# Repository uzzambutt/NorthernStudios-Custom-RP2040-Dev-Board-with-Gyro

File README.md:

# NorthernStudios-Custom-RP2040-Dev-Board-with-Gyro

***Schematic***

## Images:
**Rendered Board**:

**Raw Routing**:

## Features
1: This dev board has a LED for power indicator.
2: This board has a 6-Axis Gyro + Accelerometer integrated in it. you can read the schematic to check it out.

## Caution:
> I have not routed the GPIO 0,1 and ADC 1 and 2 because of spacing problems. there was not enough space to route them because the accelerometer had covered most of that space. 

---
> Made By uzzam for NorthernStudios.
> Funded By HackClub.
> 04/12/2025
> uzzambutt1@outlook.com

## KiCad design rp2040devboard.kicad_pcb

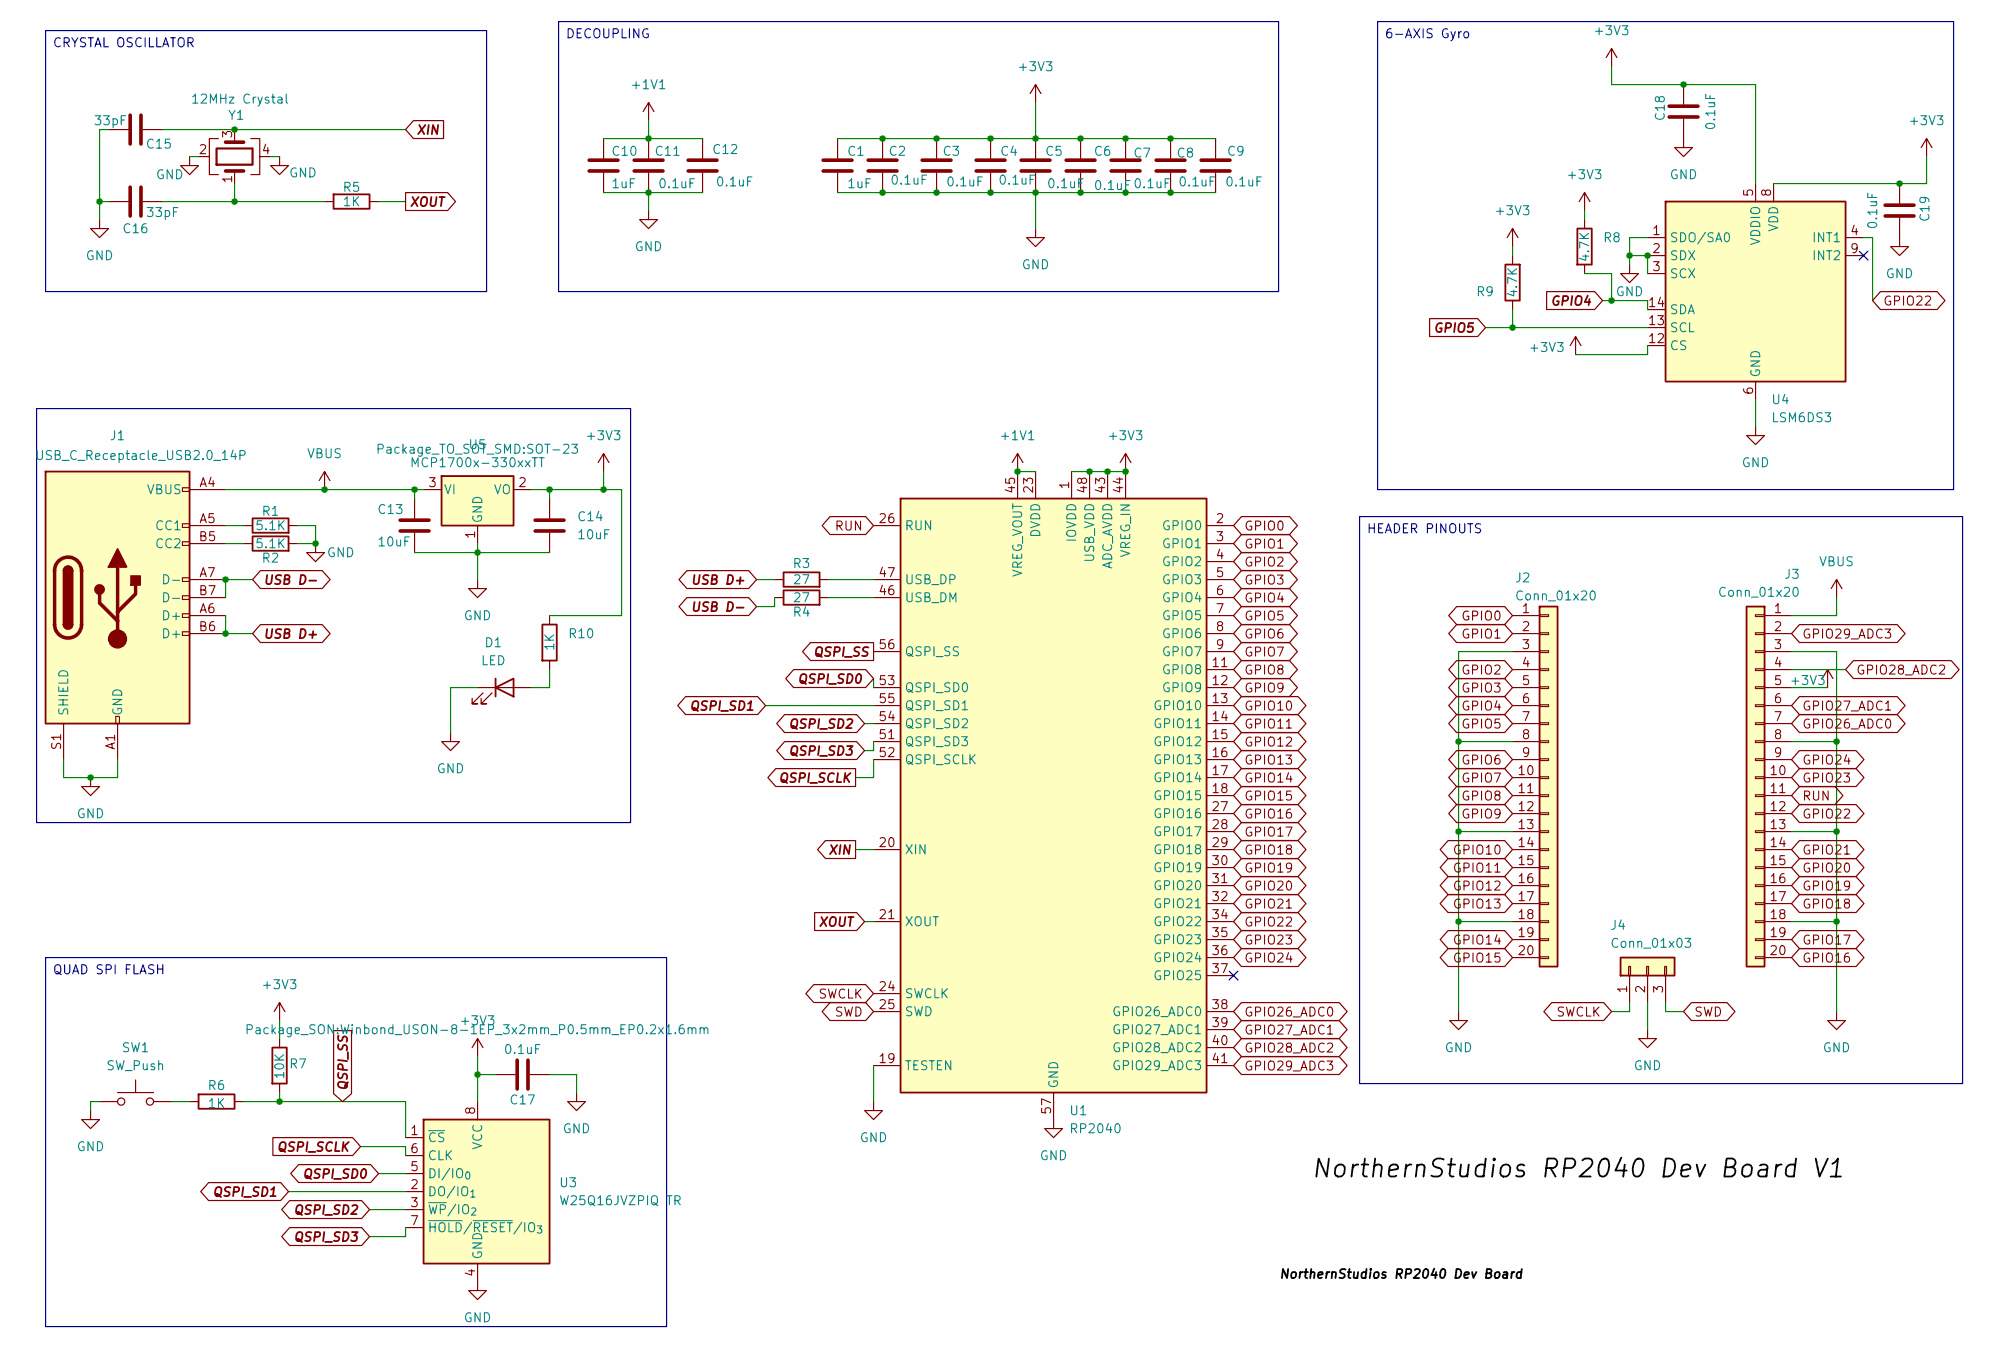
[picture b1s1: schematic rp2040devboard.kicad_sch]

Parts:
C1, C10: 1uF; C_0402_1005Metric
C2, C3, C4, C5, C6, C7, C8, C9, C11, C12, C17, C18, C19: 0.1uF; C_0402_1005Metric
C13, C14: 10uF; C_0603_1608Metric
C15, C16: 33pF; C_0402_1005Metric
D1: LED; LED_01005_0402Metric
J1: USB_C_Receptacle_USB2.0_14P; USB_C_Receptacle_HRO_TYPE-C-31-M-12
J2, J3: Conn_01x20; PinHeader_1x20_P2.54mm_Vertical
J4: Conn_01x03; PinHeader_1x03_P2.54mm_Vertical
R1, R2: 5.1K; R_0402_1005Metric
R3, R4: 27; R_0402_1005Metric
R5, R6, R10: 1K; R_0402_1005Metric
R7: 10K; R_0402_1005Metric
R8, R9: 4.7K; R_0402_1005Metric
SW1: SW_Push; SW_Push_SPST_NO_Alps_SKRK
U1: RP2040; QFN-56-1EP_7x7mm_P0.4mm_EP3.2x3.2mm
U3: W25Q16JVZPIQ TR; Winbond_USON-8-1EP_3x2mm_P0.5mm_EP0.2x1.6mm
U4: LSM6DS3; LGA-14_3x2.5mm_P0.5mm_LayoutBorder3x4y
U5: MCP1700x-330xxTT; SOT-23
Y1: 12MHz Crystal; Crystal_SMD_3225-4Pin_3.2x2.5mm

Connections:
+1V1: C10.1, C11.1, C12.1, U1.23 (DVDD), U1.45 (VREG_VOUT), U1.50 (DVDD)
+3V3: C1.1, C2.1, C3.1, C4.1, C5.1, C6.1, C7.1, C8.1, C9.1, C14.1, C17.1, C18.1, C19.2, J3.5, R7.1, R8.1, R9.2, R10.1, U1.1 (IOVDD), U1.10 (IOVDD), U1.22 (IOVDD), U1.33 (IOVDD), U1.42 (IOVDD), U1.43 (ADC_AVDD), U1.44 (VREG_IN), U1.48 (USB_VDD), U1.49 (IOVDD), U3.8 (VCC), U4.5 (VDDIO), U4.8 (VDD), U4.12 (CS), U5.2 (VO)
GND: C1.2, C2.2, C3.2, C4.2, C5.2, C6.2, C7.2, C8.2, C9.2, C10.2, C11.2, C12.2, C13.1, C14.2, C15.1, C16.1, C17.2, C18.2, C19.1, D1.1 (K), J1.A1 (GND), J1.A12 (GND), J1.B1 (GND), J1.B12 (GND), J1.S1 (SHIELD), J2.3, J2.8, J2.13, J2.18, J3.3, J3.8, J3.13, J3.18, J4.2, R1.2, R2.2, SW1.1, U1.19 (TESTEN), U1.57 (GND), U3.4 (GND), U4.1 (SDO/SA0), U4.2 (SDX), U4.3 (SCX), U4.6 (GND), U4.7 (GND), U5.1 (GND), Y1.2, Y1.4
GPIO0: J2.1, U1.2 (GPIO0)
GPIO1: J2.2, U1.3 (GPIO1)
GPIO2: J2.4, U1.4 (GPIO2)
GPIO3: J2.5, U1.5 (GPIO3)
GPIO4: J2.6, R8.2, U1.6 (GPIO4), U4.14 (SDA)
GPIO5: J2.7, R9.1, U1.7 (GPIO5), U4.13 (SCL)
GPIO6: J2.9, U1.8 (GPIO6)
GPIO7: J2.10, U1.9 (GPIO7)
GPIO8: J2.11, U1.11 (GPIO8)
GPIO9: J2.12, U1.12 (GPIO9)
GPIO10: J2.14, U1.13 (GPIO10)
GPIO11: J2.15, U1.14 (GPIO11)
GPIO12: J2.16, U1.15 (GPIO12)
GPIO13: J2.17, U1.16 (GPIO13)
GPIO14: J2.19, U1.17 (GPIO14)
GPIO15: J2.20, U1.18 (GPIO15)
GPIO16: J3.20, U1.27 (GPIO16)
GPIO17: J3.19, U1.28 (GPIO17)
GPIO18: J3.17, U1.29 (GPIO18)
GPIO19: J3.16, U1.30 (GPIO19)
GPIO20: J3.15, U1.31 (GPIO20)
GPIO21: J3.14, U1.32 (GPIO21)
GPIO22: J3.12, U1.34 (GPIO22), U4.4 (INT1)
GPIO23: J3.10, U1.35 (GPIO23)
GPIO24: J3.9, U1.36 (GPIO24)
GPIO26_ADC0: J3.7, U1.38 (GPIO26_ADC0)
GPIO27_ADC1: J3.6, U1.39 (GPIO27_ADC1)
GPIO28_ADC2: J3.4, U1.40 (GPIO28_ADC2)
GPIO29_ADC3: J3.2, U1.41 (GPIO29_ADC3)
unnamed: C16.2, R5.2, Y1.1
unnamed: D1.2 (A), R10.2
unnamed: J1.A5 (CC1), R1.1
unnamed: J1.B5 (CC2), R2.1
unnamed: R6.2, SW1.2
unnamed: R4.2, U1.46 (USB_DM)
unnamed: R3.2, U1.47 (USB_DP)
QSPI_SCLK: U1.52 (QSPI_SCLK), U3.6 (CLK)
QSPI_SD0: U1.53 (QSPI_SD0), U3.5 (DI/IO_{0})
QSPI_SD1: U1.55 (QSPI_SD1), U3.2 (DO/IO_{1})
QSPI_SD2: U1.54 (QSPI_SD2), U3.3 (~WP/IO_{2})
QSPI_SD3: U1.51 (QSPI_SD3), U3.7 (~HOLD/~RESET/IO_{3})
QSPI_SS: R6.1, R7.2, U1.56 (QSPI_SS), U3.1 (~CS)
RUN: J3.11, U1.26 (RUN)
SWCLK: J4.1, U1.24 (SWCLK)
SWD: J4.3, U1.25 (SWD)
USB D+: J1.A6 (D+), J1.B6 (D+), R3.1
USB D-: J1.A7 (D-), J1.B7 (D-), R4.1
VBUS: C13.2, J1.A4 (VBUS), J1.A9 (VBUS), J1.B4 (VBUS), J1.B9 (VBUS), J3.1, U5.3 (VI)
XIN: C15.2, U1.20 (XIN), Y1.3
XOUT: R5.1, U1.21 (XOUT)

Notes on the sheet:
QUAD SPI FLASH
HEADER PINOUTS
DECOUPLING
6-AXIS Gyro
CRYSTAL OSCILLATOR

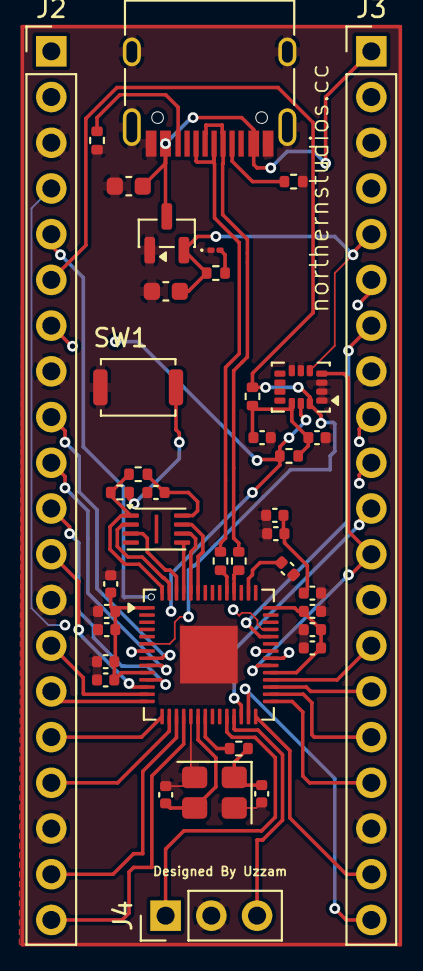
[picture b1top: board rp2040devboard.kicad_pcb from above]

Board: 6 copper layers, 40 parts (0 on the bottom side), 53 nets.

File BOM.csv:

"Reference","Qty","Value","DNP","Exclude from BOM","Exclude from Board","Footprint","Datasheet"
"C1,C10","2","1uF","","","","Capacitor_SMD:C_0402_1005Metric","~"
"C2,C3,C4,C5,C6,C7,C8,C9,C11,C12,C17,C18,C19","13","0.1uF","","","","Capacitor_SMD:C_0402_1005Metric","~"
"C13,C14","2","10uF","","","","Capacitor_SMD:C_0603_1608Metric","~"
"C15,C16","2","33pF","","","","Capacitor_SMD:C_0402_1005Metric","~"
"D1","1","LED","","","","LED_SMD:LED_01005_0402Metric","~"
"J1","1","USB_C_Receptacle_USB2.0_14P","","","","Connector_USB:USB_C_Receptacle_HRO_TYPE-C-31-M-12","https://www.usb.org/sites/default/files/documents/usb_type-c.zip"
"J2,J3","2","Conn_01x20","","","","Connector_PinHeader_2.54mm:PinHeader_1x20_P2.54mm_Vertical","~"
"J4","1","Conn_01x03","","","","Connector_PinHeader_2.54mm:PinHeader_1x03_P2.54mm_Vertical","~"
"R1,R2","2","5.1K","","","","Resistor_SMD:R_0402_1005Metric","~"
"R3,R4","2","27","","","","Resistor_SMD:R_0402_1005Metric","~"
"R5,R6,R10","3","1K","","","","Resistor_SMD:R_0402_1005Metric","~"
"R7","1","10K","","","","Resistor_SMD:R_0402_1005Metric","~"
"R8,R9","2","4.7K","","","","Resistor_SMD:R_0402_1005Metric","~"
"SW1","1","SW_Push","","","","Button_Switch_SMD:SW_Push_SPST_NO_Alps_SKRK","~"
"U1","1","RP2040","","","","Package_DFN_QFN:QFN-56-1EP_7x7mm_P0.4mm_EP3.2x3.2mm","https://datasheets.raspberrypi.com/rp2040/rp2040-datasheet.pdf"
"U3","1","W25Q16JVZPIQ TR","","","","Package_SON:Winbond_USON-8-1EP_3x2mm_P0.5mm_EP0.2x1.6mm","https://www.winbond.com/resource-files/w25q128jv_dtr%20revc%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"
"U4","1","LSM6DS3","","","","Package_LGA:LGA-14_3x2.5mm_P0.5mm_LayoutBorder3x4y","https://www.st.com/resource/en/datasheet/lsm6ds3tr-c.pdf"
"U5","1","MCP1700x-330xxTT","","","","Package_TO_SOT_SMD:SOT-23","http://ww1.microchip.com/downloads/en/DeviceDoc/20001826D.pdf"
"Y1","1","12MHz Crystal","","","","Crystal:Crystal_SMD_3225-4Pin_3.2x2.5mm","~"

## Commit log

2025-12-04 Create e
